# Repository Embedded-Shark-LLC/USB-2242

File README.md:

# USB-2242
This is a project to integrate a Logitech&trade; Unifying Receiver internally for laptops.  Specifically, I designed this to fit an M.2 2242 slot (M+B key) for my Thinkpad X1C6 (replacing the WWAN card).

If space permits, any low-power USB device (under 500 mA) can be plugged into this adapter.

## Features
- M.2 2242 form factor for internal installation
- Optional USB-A receptacle solder pads for testing/thicker laptops
- PCB cutout for minimum height when not using USB-A receptacle
- Resettable fuse to avoid overcurrent/short circuit damage

## Concept
Most thin and light laptops have a limited number of USB ports, especially USB-A ports.  Currently, my Thinkpad X1C6 has 2 USB-C and 2 USB-A ports, and I constantly leave my wireless mouse receiver in one of the USB-A ports.

After seeing similar products available for older laptop models, I couldn't find one that fit in my M.2 2242 slot, so I made my own.  All it does is provide 5V power for the USB device and routes the USB data lines according to the [M.2 specification](https://pcisig.com/specifications/pciexpress/M.2_Specification/) (local copy available [here](docs/SPEC_PCIe-M.2-Rev1.0.pdf)).

## Notice
PCB thickness must be 0.8 mm to fit in standard M.2 slots.

## Planned Features
- Separate flex PCB for easier soldering of "floating" USB device

## PCB Renders
|PCB Front|PCB Back|
|---------|--------|
|||

## Trademark Notice
_Logitech, Logi, and their logos are trademarks or registered trademarks of Logitech Europe S.A. and/or its affiliates in the United States and/or other countries._

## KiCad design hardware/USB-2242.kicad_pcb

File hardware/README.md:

# Hardware

## Major components
| Description           | Part Number           | Manufacturer          | Comments                          |
| --------------------- | --------------------- | --------------------- | --------------------------------- |
| USB A port            | USB-A-S-RA-TSMT       | Adam Tech             | SMD, right angle                  |
| Boost converter       | TPS613222ADBVR        | Texas Instruments     | 5 V,  2.5 A                       |

## Minor components
| Description           | Part Number           | Manufacturer          | Comments                          |
| --------------------- | --------------------- | --------------------- | --------------------------------- |
| Resettable fuse       | SMD0603B050TF         | YAGEO                 | 500 mA hold, 1 A trip, 6 V max    |
| Schottky diode        | CUS15S30,H3F          | Toshiba Semiconductor | 30 V, 1.5 A                       |

## Passive components
| Description           | Part Number           | Manufacturer          | Comments                          |
| --------------------- | --------------------- | --------------------- | --------------------------------- |
| 4.99 R resistor       | RC0402FR0-74R99L      | YAGEO                 | 0402                              |
| 1 nF capacitor        | 04025C102KAT2A        | KYOCERA               | 50 V, X7R, 0402                   |
| 100 nF capacitor      | CL05A104KA5NNNC       | Samsung               | 25 V, X5R, 0402                   |
| 10 uF capacitor       | GRM155R60J106ME05D    | Murata Electronics    | 6.3 V, X5R, 0402                  |
| 22 uF capacitor       | CM05X5R226M06AH080    | KYOCERA               | 6.3 V, X5R, 0402                  |
| 2.2 uH inductor       | CIGW252010GL2R2MNE    | Samsung               | 93 mR DCR, 1008                   |

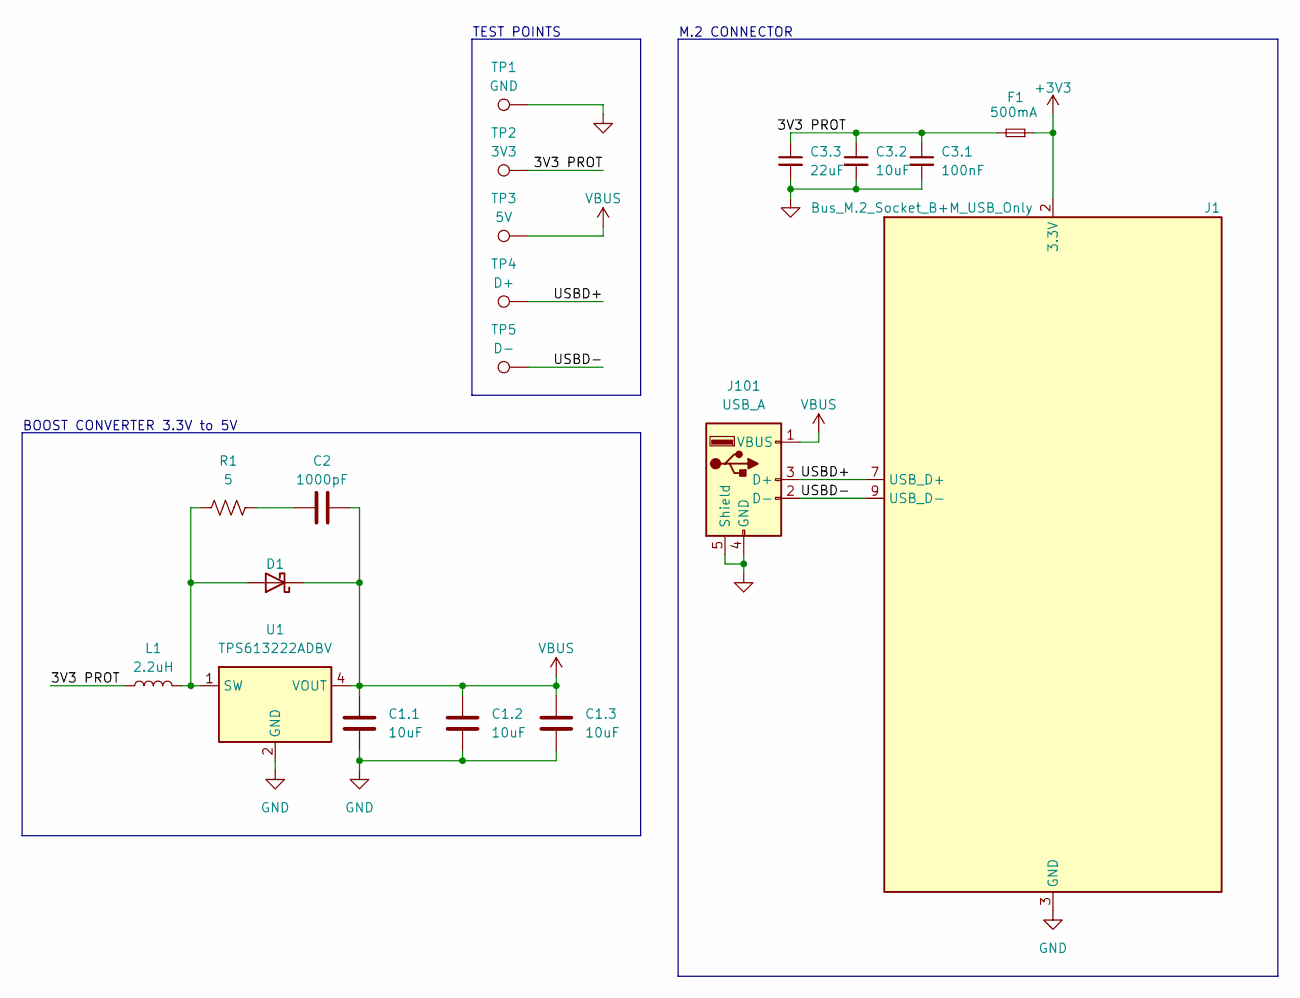
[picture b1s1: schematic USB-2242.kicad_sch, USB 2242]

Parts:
C1.1, C1.2, C1.3, C3.2: 10uF; C_0402_1005Metric_Pad0.74x0.62mm_HandSolder
C2: 1000pF; C_0402_1005Metric_Pad0.74x0.62mm_HandSolder
C3.1: 100nF; C_0402_1005Metric_Pad0.74x0.62mm_HandSolder
C3.3: 22uF; C_0402_1005Metric_Pad0.74x0.62mm_HandSolder
D1: D_Schottky; D_SOD-323
F1: 500mA; Fuse_0603_1608Metric_Pad1.05x0.95mm_HandSolder
J1: Bus_M.2_Socket_B+M_USB_Only; M.2-2242-B+M-KEY_USB-ONLY
J101: USB_A; USB-A-S-RA-TSMT
L1: 2.2uH; L_1008_2520Metric_Pad1.43x2.20mm_HandSolder
R1: 5; R_0402_1005Metric_Pad0.72x0.64mm_HandSolder
TP1: GND; TestPoint_Pad_D1.0mm
TP2: 3V3; TestPoint_Pad_D1.0mm
TP3: 5V; TestPoint_Pad_D1.0mm
TP4: D+; TestPoint_Pad_D1.0mm
TP5: D-; TestPoint_Pad_D1.0mm
U1: TPS613222ADBV; SOT-23-5

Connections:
+3V3: F1.1, J1.2 (3.3V), J1.4 (3.3V), J1.70 (3.3V), J1.72 (3.3V), J1.74 (3.3V)
/3V3 PROT: C3.1.1, C3.2.1, C3.3.1, F1.2, L1.1, TP2.1
/USBD+: J1.7 (USB_D+), J101.3 (D+), TP4.1
/USBD-: J1.9 (USB_D-), J101.2 (D-), TP5.1
GND: C1.1.2, C1.2.2, C1.3.2, C3.1.2, C3.2.2, C3.3.2, J1.3 (GND), J1.5 (GND), J1.11 (GND), J1.27 (GND), J1.33 (GND), J1.39 (GND), J1.45 (GND), J1.51 (GND), J1.57 (GND), J1.71 (GND), J1.73 (GND), J101.4 (GND), J101.5 (Shield), TP1.1, U1.2 (GND)
unnamed: C2.1, R1.2
unnamed: D1.2 (A), L1.2, R1.1, U1.1 (SW)
VBUS: C1.1.1, C1.2.1, C1.3.1, C2.2, D1.1 (K), J101.1 (VBUS), TP3.1, U1.4 (VOUT)

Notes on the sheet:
M.2 CONNECTOR
TEST POINTS
BOOST CONVERTER 3.3V to 5V

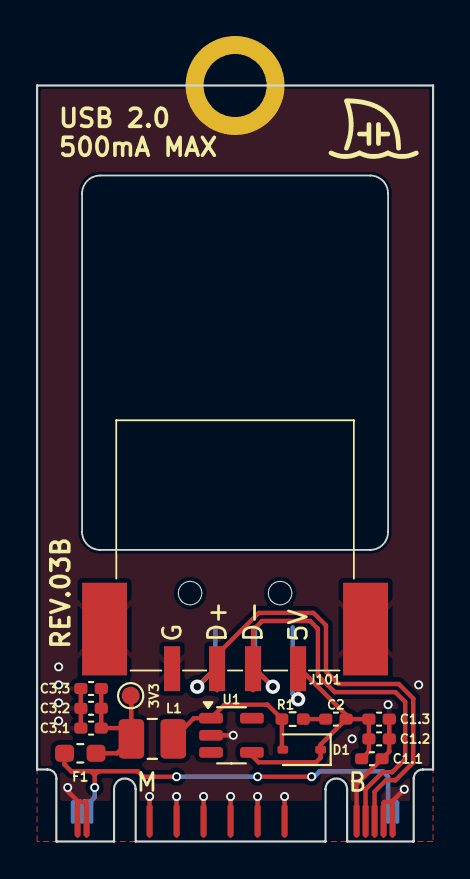
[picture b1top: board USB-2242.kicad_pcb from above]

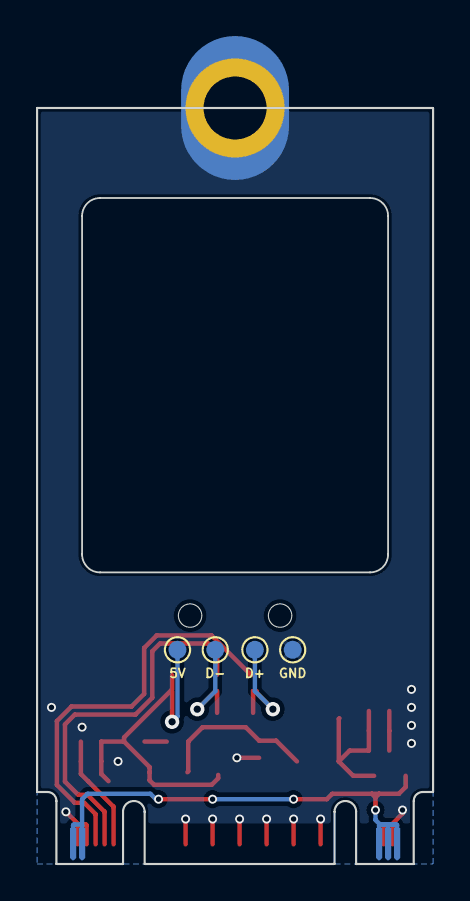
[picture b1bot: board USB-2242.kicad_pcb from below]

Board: 2 copper layers, 22.0 x 42.0 mm, 19 parts (4 on the bottom side), 8 nets.

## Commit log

2023-01-25 Update README for project
2023-01-28 Fix overlapping pad in M.2 footprints
2023-01-28 Finish layout and routing
2023-01-28 Add PCB text
2023-01-28 Reduce fill clearance and add more GND vias
2023-01-28 Add ibom
2023-01-28 Add gerber files
2023-02-01 Update pad clearance
2023-02-01 Add cutout for low-clearance use
2023-02-01 Update production files
2023-02-04 Update BOMs
2023-03-04 Change screw hole pad and PCB text
2023-03-04 Update M.2 footprints
2023-03-04 Add keepout zone above edge pads
2023-03-04 Update footprint and board settings (via size, pours, etc)
2023-03-05 Reroute after added fuse and new footprints
2023-03-05 Add test points (#1) and other finishing touches
2023-03-05 Add missing net names
2023-03-05 Update schematic date and revision
2023-03-05 Copper cleanup
2023-03-05 Update BOM
2023-03-05 Add drawings and renders
2023-03-05 Timestamp updates
2023-03-05 Move drawings/renders to CAD folder
2023-03-05 Remove random footprint
2023-03-05 Adjust M.2 keepout zones
2023-03-05 Adjust ground vias
2023-03-05 Update render images
2023-03-05 Small copper fixes
2023-03-05 Generate gerber files
2023-03-05 Update renders
2023-04-04 Update after testing and installation
2024-09-01 Change project structure
2024-09-01 Update project name to respect trademarks
2024-09-01 Add trademark notice
2024-09-01 Replace USB port and make various minor changes to project
2024-09-01 Update libraries
2024-09-01 Add notice about PCB thickness
2024-09-02 Update clearances for copper to board edge
2024-09-02 Add DRC exclusions
2024-09-14 Clean up silkscreen
2024-09-15 Create LICENSE
2024-09-15 Update LICENSE
